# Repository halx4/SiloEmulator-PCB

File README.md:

SiloEmulator-PCB

details on https://halx4.github.io/posts/SiloEmulator/

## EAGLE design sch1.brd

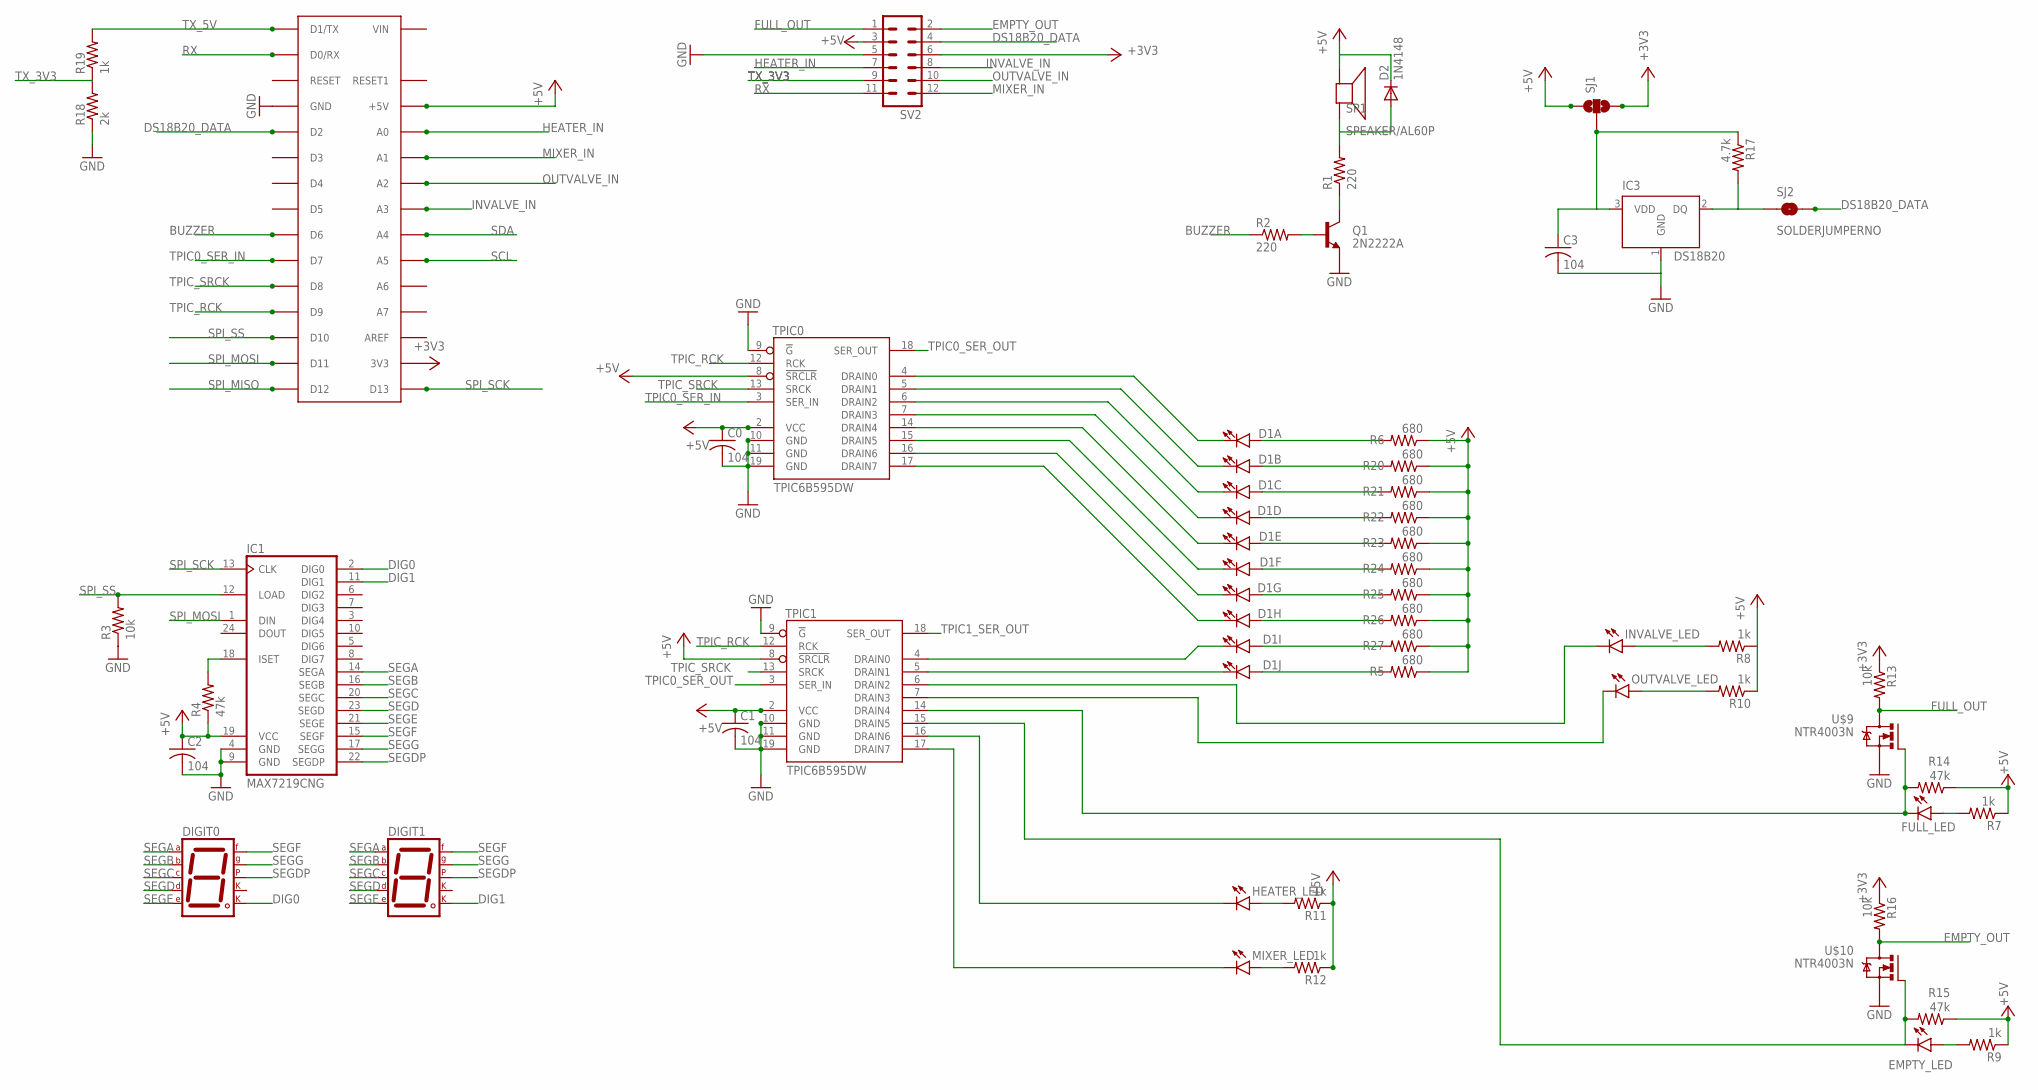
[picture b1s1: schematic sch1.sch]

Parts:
ARDUINO: ARDUINONANO; PDIP-32
C0, C1, C2, C3: 104; C0603
D1: LED_BARGRAPH_10; LED_BARGAPH_10
D2: 1N4148; DO35-7
DIGIT0, DIGIT1: 7SEG-CK; 7SEG-13
EMPTY_LED: LED0603; LED-0603
FULL_LED: LED0603; LED-0603
HEATER_LED: LED0603; LED-0603
IC1: MAX7219CNG; DIL24-3
IC3: DS18B20; TO-92
INVALVE_LED: LED0603; LED-0603
MIXER_LED: LED0603; LED-0603
OUTVALVE_LED: LED0603; LED-0603
Q1: 2N2222A; SOT23-3
R1, R2: 220; R0603
R3, R13, R16: 10k; R0603
R4, R14, R15: 47k; R0603
R5, R6, R20, R21, R22, R23, R24, R25, R26, R27: 680; R0603
R7, R8, R9, R10, R11, R12, R19: 1k; R0603
R17: 4.7k; R0603
R18: 2k; R0603
SJ1: SOLDERJUMPER_2WAYS; SJ_3
SJ2: SOLDERJUMPERNO; SJ_2S-NO
SP1: SPEAKER/AL60P; AL60P
SV2: MA06-2
TPIC0, TPIC1: TPIC6B595DW; SO20W
U$9, U$10: NTR4003N; SOT23

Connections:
+3V3: ARDUINO.17 (3V3), R13.1, R16.1, SJ1.3, SV2.6
+5V: ARDUINO.27 (+5V), C0.1, C1.1, C2.1, D2.C, IC1.19 (VCC), R4.1, R5.1, R6.1, R7.1, R8.1, R9.1, R10.1, R11.1, R12.1, R14.1, R15.1, R20.1, R21.1, R22.1, R23.1, R24.1, R25.1, R26.1, R27.1, SJ1.1, SP1.1 (+), SV2.3, TPIC0.2 (VCC), TPIC0.8 (!SRCLR), TPIC1.2 (VCC), TPIC1.8 (!SRCLR)
BUZZER: ARDUINO.9 (D6), R2.1
DIG0: DIGIT0.8 (CK2), IC1.2 (DIG0)
DIG1: DIGIT1.8 (CK2), IC1.11 (DIG1)
DS18B20_DATA: ARDUINO.5 (D2), SJ2.2, SV2.4
EMPTY_OUT: R16.2, SV2.2, U$10.3 (D)
FULL_OUT: R13.2, SV2.1, U$9.3 (D)
GND: ARDUINO.4 (GND), ARDUINO.29 (GND), C0.2, C1.2, C2.2, C3.2, IC1.4 (GND), IC1.9 (GND), IC3.1 (GND), Q1.2 (E), R3.1, R18.1, SV2.5, TPIC0.9 (!G), TPIC0.10 (GND), TPIC0.11 (GND), TPIC0.19 (GND), TPIC1.9 (!G), TPIC1.10 (GND), TPIC1.11 (GND), TPIC1.19 (GND), U$9.2 (S), U$10.2 (S)
HEATER_IN: ARDUINO.19 (A0), SV2.7
INVALVE_IN: ARDUINO.22 (A3), SV2.8
MIXER_IN: ARDUINO.20 (A1), SV2.12
unnamed: D1.2 (A), R20.2
unnamed: D1.1 (A), R6.2
unnamed: FULL_LED.A, R7.2
unnamed: INVALVE_LED.A, R8.2
unnamed: D1.16 (C), TPIC0.14 (DRAIN4)
unnamed: D1.15 (C), TPIC0.15 (DRAIN5)
unnamed: D1.3 (A), R21.2
unnamed: D1.13 (C), TPIC0.17 (DRAIN7)
unnamed: D1.12 (C), TPIC1.4 (DRAIN0)
unnamed: D1.11 (C), TPIC1.5 (DRAIN1)
unnamed: EMPTY_LED.C, R15.2, TPIC1.15 (DRAIN5), U$10.1 (G)
unnamed: OUTVALVE_LED.C, TPIC1.7 (DRAIN3)
unnamed: HEATER_LED.C, TPIC1.16 (DRAIN6)
unnamed: MIXER_LED.C, TPIC1.17 (DRAIN7)
unnamed: INVALVE_LED.C, TPIC1.6 (DRAIN2)
unnamed: D2.A, R1.2, SP1.2 (-)
unnamed: FULL_LED.C, R14.2, TPIC1.14 (DRAIN4), U$9.1 (G)
unnamed: Q1.3 (C), R1.1
unnamed: Q1.1 (B), R2.2
unnamed: IC1.18 (ISET), R4.2
unnamed: D1.14 (C), TPIC0.16 (DRAIN6)
unnamed: D1.20 (C), TPIC0.4 (DRAIN0)
unnamed: D1.19 (C), TPIC0.5 (DRAIN1)
unnamed: D1.18 (C), TPIC0.6 (DRAIN2)
unnamed: D1.17 (C), TPIC0.7 (DRAIN3)
unnamed: D1.4 (A), R22.2
unnamed: D1.5 (A), R23.2
unnamed: D1.6 (A), R24.2
unnamed: D1.7 (A), R25.2
unnamed: D1.8 (A), R26.2
unnamed: D1.9 (A), R27.2
unnamed: D1.10 (A), R5.2
unnamed: C3.1, IC3.3 (VDD), R17.1, SJ1.2
unnamed: IC3.2 (DQ), R17.2, SJ2.1
unnamed: EMPTY_LED.A, R9.2
unnamed: OUTVALVE_LED.A, R10.2
unnamed: HEATER_LED.A, R11.2
unnamed: MIXER_LED.A, R12.2
OUTVALVE_IN: ARDUINO.21 (A2), SV2.10
RX: ARDUINO.2 (D0/RX), SV2.11
SCL: ARDUINO.24 (A5)
SDA: ARDUINO.23 (A4)
SEGA: DIGIT0.7 (A), DIGIT1.7 (A), IC1.14 (SEGA)
SEGB: DIGIT0.6 (B), DIGIT1.6 (B), IC1.16 (SEGB)
SEGC: DIGIT0.4 (C), DIGIT1.4 (C), IC1.20 (SEGC)
SEGD: DIGIT0.2 (D), DIGIT1.2 (D), IC1.23 (SEGD)
SEGDP: DIGIT0.5 (DP), DIGIT1.5 (DP), IC1.22 (SEGDP)
SEGE: DIGIT0.1 (E), DIGIT1.1 (E), IC1.21 (SEGE)
SEGF: DIGIT0.9 (F), DIGIT1.9 (F), IC1.15 (SEGF)
SEGG: DIGIT0.10 (G), DIGIT1.10 (G), IC1.17 (SEGG)
SPI_MISO: ARDUINO.15 (D12)
SPI_MOSI: ARDUINO.14 (D11), IC1.1 (DIN)
SPI_SCK: ARDUINO.16 (D13), IC1.13 (CLK)
SPI_SS: ARDUINO.13 (D10), IC1.12 (LOAD), R3.2
TPIC0_SER_IN: ARDUINO.10 (D7), TPIC0.3 (SER_IN)
TPIC0_SER_OUT: TPIC0.18 (SER_OUT), TPIC1.3 (SER_IN)
TPIC1_SER_OUT: TPIC1.18 (SER_OUT)
TPIC_RCK: ARDUINO.12 (D9), TPIC0.12 (RCK), TPIC1.12 (RCK)
TPIC_SRCK: ARDUINO.11 (D8), TPIC0.13 (SRCK), TPIC1.13 (SRCK)
TX_3V3: R18.2, R19.1, SV2.9
TX_5V: ARDUINO.1 (D1/TX), R19.2

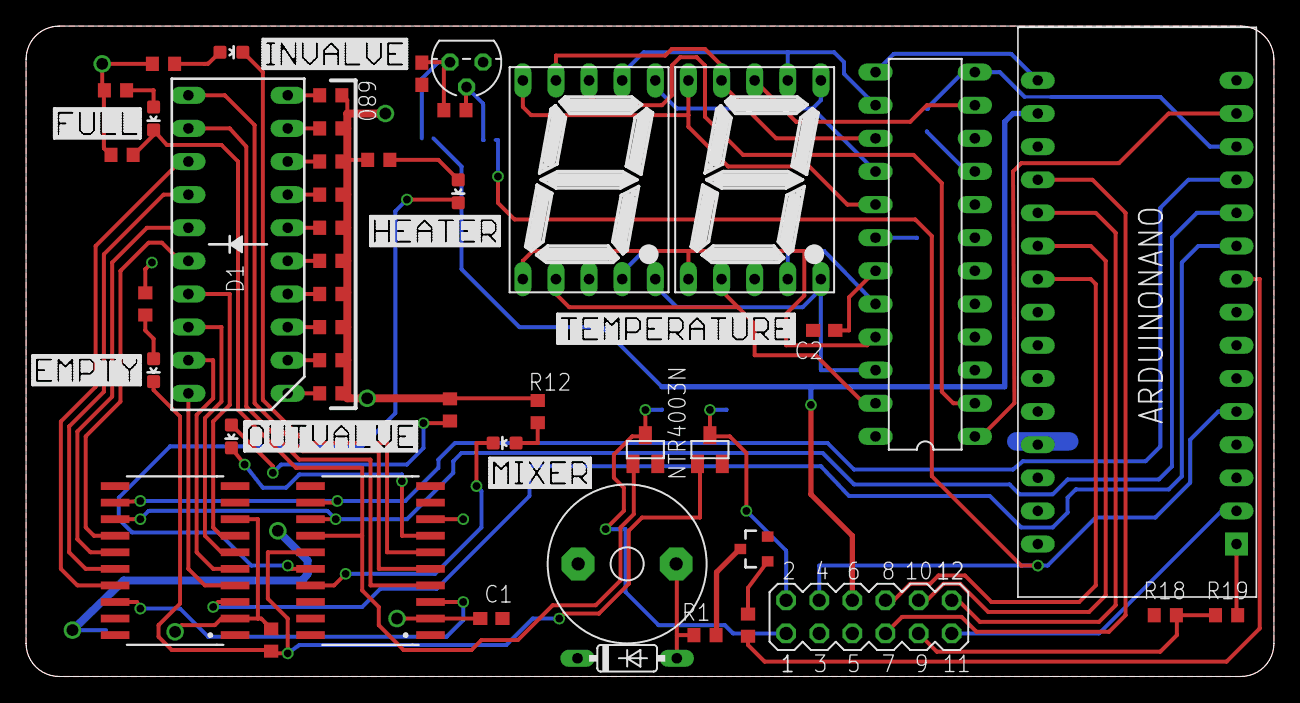
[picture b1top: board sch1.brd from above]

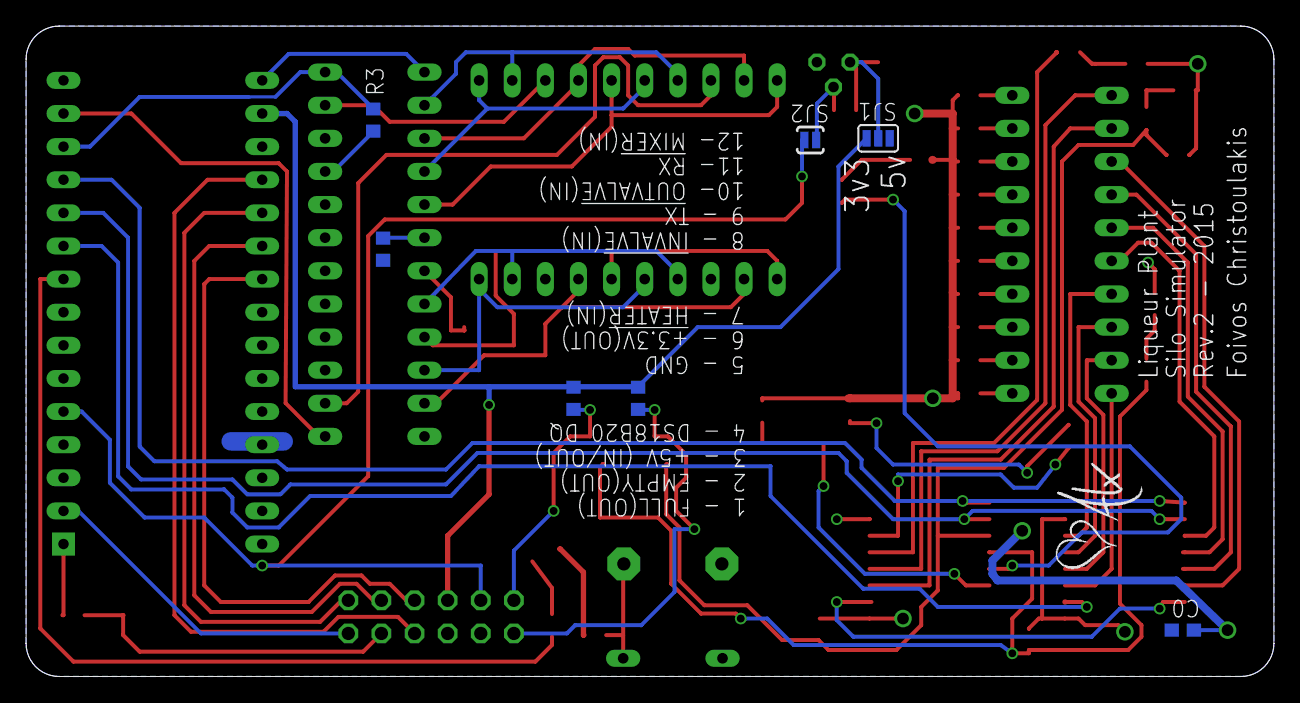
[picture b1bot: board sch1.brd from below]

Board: 2 copper layers, 95.7 x 49.9 mm, 61 parts (8 on the bottom side), 69 nets.

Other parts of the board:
U$1: HALX2_532_SILKSCREEN
U$2: INVALVE70
U$3: FULL70
U$4: EMPTY70
U$5: OUTVALVE70
U$6: TEMPERATURE70
U$7: MIXER70
U$8: HEATER70

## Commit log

2017-07-24 init commit

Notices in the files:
parts and their libraries:
SparkFun-LED: Licensing: Creative Commons ShareAlike 4.0 International - https://creativecommons.org/licenses/by-sa/4.0
